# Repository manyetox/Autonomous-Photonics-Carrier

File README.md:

# Autonomous-Photonics-Carrier

**A source-available mobile robotics platform for autonomous and reconfigurable free-space photonics experiments.**

This repository contains the electronics, fabrication files, preliminary embedded firmware, and research documentation for my UCL Electrical and Electronic Engineering third-year BEng project. The carrier is intended to move standard optical hardware around a tabletop, estimate its own motion from complementary sensors, and ultimately support closed-loop optical experiment setup and alignment.

> **Project status — 29 October 2026:** **Platform V2 works**, including the motors, BNO086 IMU, and PAW3395 optical-flow sensor. The **MA730 magnetic encoders remain untested because of component-ordering delays**. **Platform V3 is now in development**, replacing the BNO086 with a lower-cost **STMicroelectronics LSM6DS3**. V3 hardware and firmware validation, full multi-sensor autonomy, and quantitative positioning experiments remain in progress. See the [V3 development notes](docs/platform-v3.md).

<p align="center">
  
  &nbsp;&nbsp;
  
</p>

<p align="center"><em>Platform V2 photographed during assembly. V2 has since been reported working; magnetic-encoder testing is still awaiting components. These photographs show V2, not the developing V3.</em></p>

## Read this first: platform versions are not board revisions

The carrier now has **three platform generations**, with V3 under development:

| System generation | Meaning | Status |
|---|---|---|
| **Platform V1** | First integrated/monolithic autonomous-photonics carrier electronics | Historical, validated, superseded by V2 |
| **Platform V2** | Modular carrier with BNO086 IMU | Working prototype; magnetic encoders still untested |
| **Platform V3** | Next carrier generation with lower-cost LSM6DS3 IMU | In development; see [V3 notes](docs/platform-v3.md) |

The numbers on individual V2 PCBs are **board-local revisions**, not new carrier generations. For example, **OFS-R2.1.1** means *Optical-Flow Sensor board revision 2.1.1*; it is still part of **Platform V2**. The same applies to **MB-R2.1**, **MDI-R2.0**, and **ENC-R1.0**.

See [`VERSIONING.md`](VERSIONING.md) before using fabrication files.

## Why this project exists

Free-space optical experiments are normally assembled and aligned manually. Even a simple setup can require repeated positioning of posts, lenses, polarisers, sources, detectors, and cameras. The long-term research question behind this project is whether a low-cost fleet of mobile optomechanical carriers can make parts of that process **reconfigurable, repeatable, measurable, and eventually autonomous**.

This repository focuses on the carrier layer: motion, embedded electronics, local sensing, and the interfaces needed for higher-level perception and closed-loop experiment control. It does **not** claim that autonomous optical alignment has already been solved; that is the experimental work this platform is intended to enable.

## Research questions

The project is being developed as an experimental research platform rather than only as a mobile-robot hardware build. The central question is:

> **Can a self-propelled optical post-holder module combine mobile positioning, multi-sensor localisation, and optical feedback to autonomously reconstruct and align repeatable free-space photonics experiments?**

The current evaluation is organised around six questions:

1. **Coarse positioning accuracy and repeatability** — How accurately can a carrier reach a commanded planar pose \((x, y, \psi)\), and how closely can it return to that pose over repeated trials? How are the results affected by approach direction, travel distance, wheel slip, payload, and table-surface conditions?
2. **Stationary stability** — How much translational and angular drift occurs while the carrier remains stationary on its wheels? How are the results affected by motor-hold strategy, payload centre of mass, battery voltage, and measurement duration?
3. **Localisation and sensor fusion** — What accuracy and robustness can be achieved using the MA730 wheel encoders, PAW3395 optical-flow sensor, BNO086 (V2) or LSM6DS3 (V3) IMU, and planned overhead visual fiducials individually and in combination? In particular, can the fused estimate remain useful during wheel slip, short visual occlusion, and accumulated odometry drift?
4. **Closed-loop optical alignment and recovery** — Can optical feedback compensate for the residual mechanical error remaining after mobile positioning? What alignment error, convergence time, capture range, success rate, and recovery behaviour can be achieved?
5. **Experiment reconstruction and operating range** — Can one or more carriers reconstruct the same optical configuration on separate occasions and reproduce the same measurement? For which beam sizes, propagation distances, wavelengths, and classes of tabletop experiment is the achieved positioning performance sufficient?
6. **Compatibility, cost, and scalability** — Can the platform carry standard optical posts and common holders without permanent modification? What payload, centre-of-mass height, battery runtime, and cost per carrier are practical, and how does operation change when multiple carriers share the same workspace?

These questions are intended to map directly onto measurable experiments. Results will only be reported after the relevant mechanical, electronic, localisation, and optical-control subsystems have been implemented and experimentally characterised.

> **Design-evolution note:** the earliest research framing included an on-carrier screw-and-flexure fine-positioning stage and UWB ranging. Those ideas belong to the earlier design direction and are **not core Platform V2 subsystems**. Platform V2 instead focuses on a modular mobile carrier using wheel encoding, bottom optical flow, inertial sensing, planned overhead visual localisation, and later optical feedback. Fine optomechanical correction can be evaluated as a separate layer if required.

## Working Platform V2 architecture

```mermaid
flowchart LR
    B["1S LiPo / external power"] --> MB["MB-R2.1<br/>ESP32-WROOM-32UE mainboard"]
    MB --> MDI["MDI-R2.0<br/>TC78H651 + BNO086"]
    MDI --> LM["Left DC gearmotor"]
    MDI --> RM["Right DC gearmotor"]

    MB --> OFS["OFS-R2.1.1<br/>PAW3395 optical-flow board"]
    MB --> ENC["ENC-R1.0<br/>MA730 wheel encoder boards"]

    OFS --> REL["Relative tabletop motion"]
    ENC --> WHEEL["Wheel angle / odometry"]
    MDI --> IMU["Inertial orientation / motion"]

    CAM["Overhead camera + fiducials<br/>planned system layer"] --> HOST["Host perception + experiment software<br/>planned"]
    HOST --> MB

    REL --> FUSION["Pose estimation / sensor fusion<br/>planned"]
    WHEEL --> FUSION
    IMU --> FUSION
    CAM --> FUSION
```

The V2 redesign deliberately separates functions across small PCBs. This makes the system easier to manufacture, debug, replace, and revise than V1's dense integrated board.

### V2 hardware at a glance

| Board ID | Function | Key devices | PCB | Current state |
|---|---|---|---|---|
| **MB-R2.1** | Main controller / power / breakout | ESP32-WROOM-32UE, NCP186 3.3 V LDO | 4-layer, ~25 × 27.1 mm | **Validated** |
| **MDI-R2.0** | Dual motor drive + IMU | TC78H651FGN, BNO086 | 4-layer, ~25 × 27 mm | **Validated** |
| **OFS-R2.1.1** | Bottom optical-flow sensing | PAW3395, AP2127K-1.8 | 2-layer, ~19.3 × 24.0 mm | **Working, author-confirmed** |
| **ENC-R1.0** | Wheel-angle sensing | MA730 magnetic encoder | 2-layer, ~20 × 16.8 mm | **Untested; component ordering delayed** |

<p align="center"><em>Platform V2 design render. V2 uses a modular electronics architecture so sensing, motor control, and the main controller can be manufactured, debugged, and revised independently.</em></p>

## Design evolution

### Platform V3 — lower-cost IMU, in development

V3 replaces the V2 BNO086 with the **STMicroelectronics LSM6DS3**, identified in the latest schematic discussion. This is a six-axis accelerometer/gyroscope; V3 needs a matching driver and host-side orientation estimation instead of the BNO086 rotation-vector interface. The supplied [V3 hardware](hardware/platform-v3/README.md) includes the two-layer MDI-R3.0 motor/IMU board and OFS-R2.2 optical board. See [V3 development notes](docs/platform-v3.md).

### Platform V1 — integrated architecture

V1 placed most functions on one approximately **50 × 50 mm, 8-layer PCB**. The design included an **ESP32-S3-WROOM-1**, **DWM3000 UWB**, **BNO086 IMU**, **two TMC5041 stepper-controller ICs**, **DRV8231 motor-driver stages**, and the associated power and USB circuitry. It was a useful integration exercise and was built around the original concept of combining coarse mobile motion with local stepper/flexure positioning.

<p align="center"><em>Platform V1 concept. The first carrier generation combined the mobile base with local optomechanical positioning and concentrated most of the electronics onto a single integrated PCB.</em></p>

### Why V2 changed direction

The current architecture intentionally moves away from putting every possible function on one carrier PCB. The main reasons were:

- **Modularity:** sensor and motor electronics can be revised without remanufacturing the controller.
- **Debuggability:** faults can be isolated board-by-board.
- **Lower manufacturing risk:** smaller boards and fewer tightly coupled subsystems.
- **Sensor strategy:** PAW3395 relative optical tracking, MA730 wheel angle, BNO086 inertial data, and planned overhead fiducials provide complementary information without retaining UWB as a core requirement.
- **Fine alignment separation:** the mobile base focuses on coarse positioning and repeatability. Very fine optical correction can be implemented as a separate optomechanical layer instead of forcing stepper/flexure hardware into every mobile carrier.
- **Cost and repeatability:** the architecture is intended to scale to multiple carriers, so unnecessary per-carrier complexity matters.

The V1 source is retained because it documents the design path and may still be useful to researchers interested in a more integrated architecture.

### Legacy reference — pre-project mobile robotics hardware

Before the dedicated photonics-carrier generations, I developed a more general mobile-robot electronics platform. It is retained in [`hardware/legacy-reference`](hardware/legacy-reference/) because several practical design lessons carried into this project, but it is **not Platform V0** and should not be treated as part of the carrier version sequence.

<p align="center"><em>Legacy mobile-robot reference design retained for engineering context. It predates the autonomous-photonics carrier and is included only to document relevant design heritage.</em></p>

## Repository map

```text
Autonomous-Photonics-Carrier/
├── hardware/
│   ├── platform-v1/                 # Historical integrated carrier
│   ├── platform-v2/
│   │   ├── mainboard/MB-R2.1/
│   │   ├── motor-driver-imu/MDI-R2.0/
│   │   ├── optical-flow/OFS-R2.1.1/
│   │   └── wheel-encoder/ENC-R1.0/
│   ├── platform-v3/                 # MDI-R3.0 and OFS-R2.2 development files
│   └── legacy-reference/            # Pre-project robot electronics; not a platform version
├── firmware/
│   ├── platform-v2/agent-v2.4/       # Latest local V2 firmware and client
│   ├── platform-v3/                  # LSM6DS3 firmware pending
│   └── preliminary/                  # Original scaffold retained
├── software/                        # Planned host-side autonomy / experiment software
├── docs/                            # Architecture, methods, validation, manufacturing notes
├── data/                            # Experimental-data conventions; no results claimed yet
├── media/                           # Image/video placeholders
├── VERSIONING.md
├── CHANGELOG.md
├── CITATION.cff
└── LICENSE.md
```

## Hardware source and fabrication files

Native **KiCad source files** are provided alongside fabrication outputs. Current fabrication packages are separated from superseded board revisions so that a Gerber revision cannot be mistaken for a platform generation.

Start here:

- [Platform V1 hardware](hardware/platform-v1/README.md)
- [Platform V2 hardware](hardware/platform-v2/README.md)
- [Platform V3 development hardware](hardware/platform-v3/README.md)
- [V2 mainboard — MB-R2.1](hardware/platform-v2/mainboard/MB-R2.1/README.md)
- [Motor/IMU — MDI-R2.0](hardware/platform-v2/motor-driver-imu/MDI-R2.0/README.md)
- [Optical flow — OFS-R2.1.1](hardware/platform-v2/optical-flow/OFS-R2.1.1/README.md)
- [Wheel encoder — ENC-R1.0](hardware/platform-v2/wheel-encoder/ENC-R1.0/README.md)
- [Manufacturing guide](docs/manufacturing.md)

The CSV BOMs in the board folders were auto-extracted from the KiCad PCB files to make review easier. **They are not a substitute for checking the schematic and part datasheets before ordering.**

## Published V2 firmware

The latest local [Agent v2.4 package](firmware/platform-v2/agent-v2.4/README.md) is included for **ESP32 + BNO086 + PAW3395**. It includes web controls, independent motor factors, level/origin calibration, relative positioning, telemetry and an Open WebUI client. ESP32 compilation and host checks are documented with the package; the author’s working-V2 report does not validate every automated action. [V3 LSM6DS3 firmware remains pending](firmware/platform-v3/README.md).

## Original preliminary firmware

A deliberately conservative PlatformIO/Arduino scaffold is included in [`firmware/preliminary`](firmware/preliminary/README.md). It establishes the intended embedded-software structure, status reporting, motor-control abstraction, serial command interface, and placeholders for BNO086, PAW3395, and MA730 integration.

It is **not the final autonomy firmware** and it is **not presented as experimentally validated software**. Peripheral signal-to-GPIO assignment is left disabled by default wherever the uploaded hardware files do not prove the final system interconnect unambiguously. This prevents a public repository from presenting guessed pin mappings as fact.

The preliminary firmware and parts of the repository/software scaffolding were prepared with assistance from **OpenAI ChatGPT 5.6** and then reviewed against the project hardware files. See [`AI_ASSISTANCE.md`](AI_ASSISTANCE.md).

## Planned sensing and autonomy stack

The intended estimation hierarchy is complementary rather than relying on a single sensor:

1. **Wheel angle / odometry:** MA730 magnetic encoders provide direct rotational information at the drivetrain.
2. **Bottom optical flow:** PAW3395 provides high-rate relative motion against the tabletop and can expose wheel-slip/odometry disagreement.
3. **IMU:** BNO086 provides the V2 inertial input; V3 adopts LSM6DS3 acceleration and angular-rate data with orientation estimation in firmware.
4. **Overhead fiducials:** a camera observing AprilTags or similar fiducials is planned as a global absolute pose reference and recovery mechanism.
5. **Optical feedback:** experimental signals can eventually be incorporated into the control loop so the carrier optimises the *optical result*, not only geometric pose.

Prototype IMU/optical-flow positioning firmware has been developed in the project. Global localisation, encoder integration, multi-carrier coordination, and optical-feedback optimisation remain development work; measured positioning performance has not yet been published.

## Research measurements this platform is intended to support

The repository is organised so that later results can be reproduced rather than reported only as a final demo. The principal measurements are:

- planar pose accuracy in **x, y, and yaw** against an external reference;
- **return-to-pose repeatability** over repeated move-away-and-return cycles;
- **stationary drift** and accumulated odometry drift;
- wheel-encoder, optical-flow, and IMU disagreement under controlled motion;
- recovery from deliberate slip or localisation error;
- carrier-to-carrier consistency if multiple units are built;
- cost per carrier and sensitivity to inexpensive mechanical components;
- success rate of a defined optical alignment task.

See [`docs/research-methodology.md`](docs/research-methodology.md) and [`docs/validation.md`](docs/validation.md). Until those experiments are complete, target resolutions or simulated estimates should not be read as measured performance.

For the research context behind the architecture, see [`docs/related-work.md`](docs/related-work.md).

## Research context and selected related work

This project sits between **robotic optical alignment**, **autonomous laboratories**, and **mobile multi-sensor robotics**. The most directly relevant prior work is summarised here; the longer discussion belongs in [`docs/related-work.md`](docs/related-work.md).

- **OptoMate / AI-Driven Robotics for Optics** demonstrates a general-purpose robotic approach to physically assembling and aligning free-space optical experiments using computer vision, robotic manipulation, and AI-assisted control [1]. It is a particularly close research neighbour, but it uses an external robotic manipulator rather than making each optical element independently mobile.
- **Choi et al.** present a closed-loop framework for robotic optical assembly, alignment, and self-recovery [2]. This is directly relevant to the carrier's long-term objective of detecting misalignment, correcting it from measurement feedback, and recovering after a disturbance.
- **Rakhmatulin et al.** review automated laser-optics alignment, including optimisation and machine-learning approaches [3]. Their review motivates treating the optical signal itself as a feedback variable rather than assuming that geometric positioning alone is sufficient.
- **Fang and Savransky** show automated alignment of a reconfigurable optical system using focal-plane sensing and Kalman filtering [4], providing an example of image-based estimation driving corrective optical motion.
- **Szymanski et al.** demonstrate the broader self-driving-laboratory concept in which robotics, measurement, and computational decision-making form a closed experimental loop [5]. The present project explores a different physical layer: making the experimental optical hardware itself reconfigurable on the tabletop.

Commercial active-alignment systems from companies such as Physik Instrumente provide useful industrial context: high-precision automated optical alignment is already practical, but such systems are generally built around dedicated stages and predefined alignment tasks rather than low-cost independently mobile optical carriers [6].

The distinction matters: this repository does **not** claim that the individual techniques above are new. The research question is whether coarse mobile positioning, complementary low-cost sensing, standard optomechanical compatibility, and closed-loop optical feedback can be combined into a scalable carrier architecture for reconfigurable free-space experiments.

## Selected references

1. S. Z. Uddin, S. Vaidya, S. Choudhary, Z. Chen, R. K. Salib, L. Huang, D. R. Englund, and M. Soljačić, **“AI-Driven Robotics for Optics,”** arXiv:2505.17985, 2025. https://doi.org/10.48550/arXiv.2505.17985
2. S. Choi, S. Vaidya, C. Silva, S. Z. Uddin, S. B. Shuvo, S. Choudhary, and M. Soljačić, **“A Framework for Closed-Loop Robotic Assembly, Alignment and Self-Recovery of Precision Optical Systems,”** arXiv:2603.21496, 2026. https://doi.org/10.48550/arXiv.2603.21496
3. I. Rakhmatulin, D. Risbridger, R. Carter, M. J. D. Esser, and M. S. Erden, **“A Review of Automation of Laser Optics Alignment with a Focus on Machine Learning Applications,”** *Optics and Lasers in Engineering*, vol. 173, 107923, 2024. https://doi.org/10.1016/j.optlaseng.2023.107923
4. J. Fang and D. Savransky, **“Automated Alignment of a Reconfigurable Optical System Using Focal-Plane Sensing and Kalman Filtering,”** arXiv:1608.07550, 2016. https://arxiv.org/abs/1608.07550
5. N. J. Szymanski *et al.*, **“An Autonomous Laboratory for the Accelerated Synthesis of Inorganic Materials,”** *Nature*, vol. 624, pp. 86–91, 2023. https://doi.org/10.1038/s41586-023-06734-w
6. PI (Physik Instrumente), **“Active Photonics Alignment Systems / Fiber Optic Alignment Stages,”** product and application documentation. https://www.pi-usa.us/en/products/photonics-alignment-solutions

## Project information

**Author:** Taylan Arslan  
**Programme:** UCL Electrical and Electronic Engineering — BEng third-year project, 2026–27  
**Project supervisor:** Prof. Kaan Akşit  
**EEE co-supervisor:** Thomas Gilbert

The supervisors are acknowledged for academic supervision; this repository is maintained by the author and is **not an official UCL product or endorsement**.

## Contributing

Research feedback, reproducibility reports, bug findings, and non-commercial improvements are welcome. Please read [`CONTRIBUTING.md`](CONTRIBUTING.md) before opening a pull request. In particular, use the versioning vocabulary above when discussing hardware revisions.

## Licensing

This repository is intentionally **source-available for non-commercial research, education, and personal experimentation**, but it does **not** grant commercial-use rights under its public licences.

- Hardware design files, documentation, diagrams, and repository media: **CC BY-NC 4.0**.
- Firmware and software: **PolyForm Noncommercial License 1.0.0**.
- Commercial use requires a **separate written commercial licence** from the author.

Because of the non-commercial restriction, this project should **not** be described as OSHWA-compliant “open-source hardware.” See [`LICENSE.md`](LICENSE.md) for the exact scope and important IP limitations.

## Safety and experimental responsibility

This is research hardware, not a certified product. Re-check power rails, polarity, motor current, battery protection/charging, connector orientation, clearances, and fabrication outputs before use. If the carrier is used around lasers or other optical sources, follow the laboratory's laser-safety procedures; this repository does not replace a risk assessment or device datasheet.

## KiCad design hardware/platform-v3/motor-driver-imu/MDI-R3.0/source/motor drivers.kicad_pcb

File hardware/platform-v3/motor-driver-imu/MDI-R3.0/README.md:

# MDI-R3.0 — motor driver + LSM6DS3

**Platform:** V3 development snapshot  
**Status:** unvalidated development design  
**PCB:** two copper layers

Replaces the V2 BNO086 with LSM6DS3 and reduces the motor/IMU PCB from four copper layers to two. The PCB is marked V3.0. The schematic contains the TC78H651FNG motor-driver symbol; its component value is `~`, so the exact purchasing code still needs BOM review.

## Files

- `source/`: supplied native KiCad project, schematic and PCB; original filenames retained.
- [Component CSV](bom/components-from-schematic.csv): extracted from the schematic, not a verified purchasing BOM.
- `fabrication/supplied/`: supplied Gerber/drill outputs.

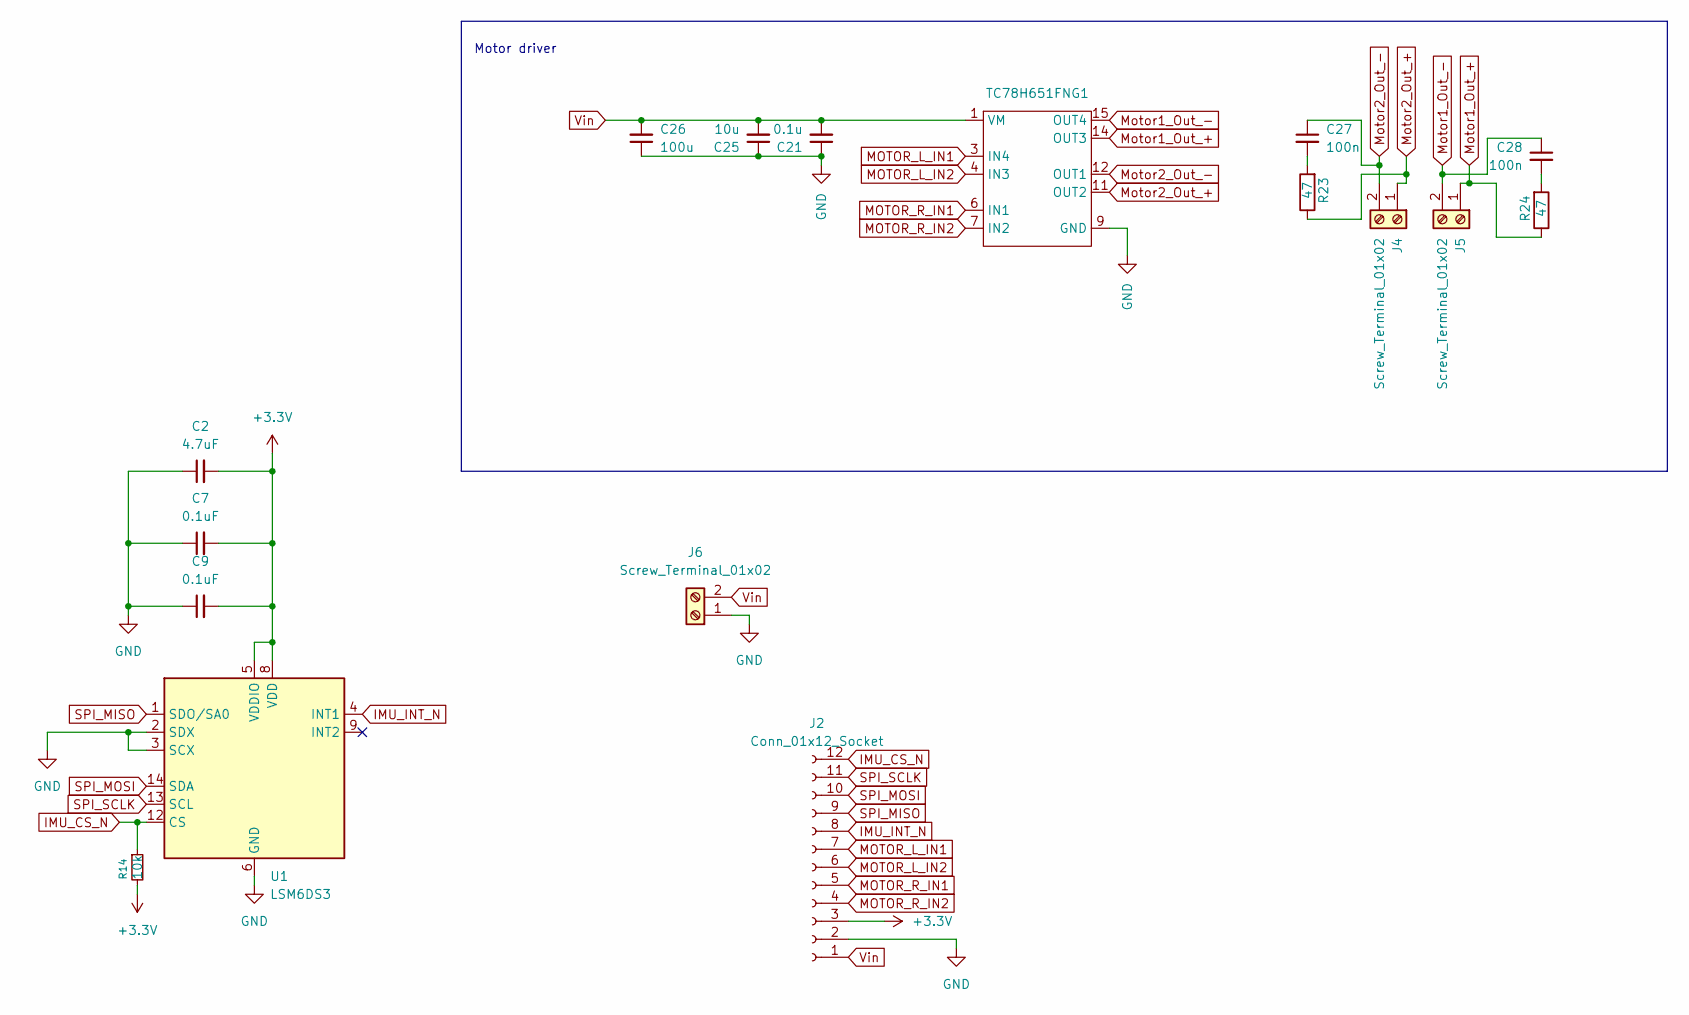
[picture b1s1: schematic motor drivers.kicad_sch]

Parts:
C2: 4.7uF; C_0805_2012Metric_Pad1.18x1.45mm_HandSolder
C7, C9: 0.1uF; C_0603_1608Metric
C21: 0.1u; C_0805_2012Metric_Pad1.18x1.45mm_HandSolder; LCSC Part # C14663
C25: 10u; C_0805_2012Metric_Pad1.18x1.45mm_HandSolder; LCSC Part # C5464883
C26: 100u; C_1206_3216Metric_Pad1.33x1.80mm_HandSolder; LCSC Part # C5464883
C27, C28: 100n; C_0603_1608Metric; LCSC Part # C14663
J2: Conn_01x12_Socket; PinHeader_1x12_P1.00mm_Vertical
J4, J5, J6: Screw_Terminal_01x02; power pad dual
R14: 10k; R_0603_1608Metric_Pad0.98x0.95mm_HandSolder
R23, R24: 47; R_0603_1608Metric; LCSC Part # C23182
TC78H651FNG1: TSSOP-16_4.4x5mm_P0.65mm
U1: LSM6DS3; LGA-14_3x2.5mm_P0.5mm_LayoutBorder3x4y

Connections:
+3.3V: C2.2, C7.2, C9.2, J2.3, R14.2, U1.5 (VDDIO), U1.8 (VDD)
GND: C2.1, C7.1, C9.1, C21.1, C25.1, C26.1, J2.2, J6.1, TC78H651FNG1.9 (GND), U1.2 (SDX), U1.3 (SCX), U1.6 (GND), U1.7 (GND)
IMU_CS_N: J2.12, R14.1, U1.12 (CS)
IMU_INT_N: J2.8, U1.4 (INT1)
MOTOR_L_IN1: J2.7, TC78H651FNG1.3 (IN4)
MOTOR_L_IN2: J2.6, TC78H651FNG1.4 (IN3)
MOTOR_R_IN1: J2.5, TC78H651FNG1.6 (IN1)
MOTOR_R_IN2: J2.4, TC78H651FNG1.7 (IN2)
Motor1_Out_+: J5.1, R24.1, TC78H651FNG1.14 (OUT3)
Motor1_Out_-: C28.1, J5.2, TC78H651FNG1.15 (OUT4)
Motor2_Out_+: J4.1, R23.1, TC78H651FNG1.11 (OUT2)
Motor2_Out_-: C27.1, J4.2, TC78H651FNG1.12 (OUT1)
unnamed: C27.2, R23.2
unnamed: C28.2, R24.2
SPI_MISO: J2.9, U1.1 (SDO/SA0)
SPI_MOSI: J2.10, U1.14 (SDA)
SPI_SCLK: J2.11, U1.13 (SCL)
Vin: C21.2, C25.2, C26.2, J2.1, J6.2, TC78H651FNG1.1 (VM)

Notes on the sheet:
Motor driver

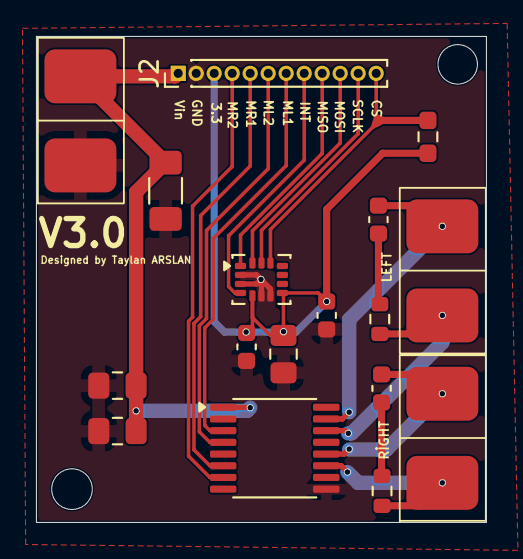
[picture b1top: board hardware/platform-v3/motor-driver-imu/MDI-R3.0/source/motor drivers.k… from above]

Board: 2 copper layers, 25.0 x 27.0 mm, 17 parts (0 on the bottom side), 18 nets.

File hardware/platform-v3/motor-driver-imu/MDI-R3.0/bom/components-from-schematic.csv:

Reference,Value,Footprint,Datasheet
C2,4.7uF,Capacitor_SMD:C_0805_2012Metric_Pad1.18x1.45mm_HandSolder,
C7,0.1uF,Capacitor_SMD:C_0603_1608Metric,
C9,0.1uF,Capacitor_SMD:C_0603_1608Metric,
C21,0.1u,Capacitor_SMD:C_0805_2012Metric_Pad1.18x1.45mm_HandSolder,
C25,10u,Capacitor_SMD:C_0805_2012Metric_Pad1.18x1.45mm_HandSolder,
C26,100u,Capacitor_SMD:C_1206_3216Metric_Pad1.33x1.80mm_HandSolder,
C27,100n,Capacitor_SMD:C_0603_1608Metric,
C28,100n,Capacitor_SMD:C_0603_1608Metric,
J2,Conn_01x12_Socket,Connector_PinHeader_1.00mm:PinHeader_1x12_P1.00mm_Vertical,
J4,Screw_Terminal_01x02,Library-kicad:power pad dual,
J5,Screw_Terminal_01x02,Library-kicad:power pad dual,
J6,Screw_Terminal_01x02,Library-kicad:power pad dual,
R14,10k,Resistor_SMD:R_0603_1608Metric_Pad0.98x0.95mm_HandSolder,
R23,47,Resistor_SMD:R_0603_1608Metric,
R24,47,Resistor_SMD:R_0603_1608Metric,
TC78H651FNG1,~,Package_SO:TSSOP-16_4.4x5mm_P0.65mm,
U1,LSM6DS3,Package_LGA:LGA-14_3x2.5mm_P0.5mm_LayoutBorder3x4y,https://www.st.com/resource/en/datasheet/lsm6ds3tr-c.pdf

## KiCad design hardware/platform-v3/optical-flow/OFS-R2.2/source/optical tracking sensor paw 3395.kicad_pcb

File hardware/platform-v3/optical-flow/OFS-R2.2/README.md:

# OFS-R2.2 — PAW3395 optical flow

**Platform:** V3 development snapshot  
**Status:** unvalidated development design  
**PCB:** two copper layers

The PCB is marked V2.2 and uses two copper layers. This is the revised optical-flow board supplied with the V3 development files; the author-confirmed working V2 sensor does not establish validation of this revision.

## Files

- `source/`: supplied native KiCad project, schematic and PCB; original filenames retained.
- [Component CSV](bom/components-from-schematic.csv): extracted from the schematic, not a verified purchasing BOM.
- `fabrication/supplied/`: supplied Gerber/drill outputs.

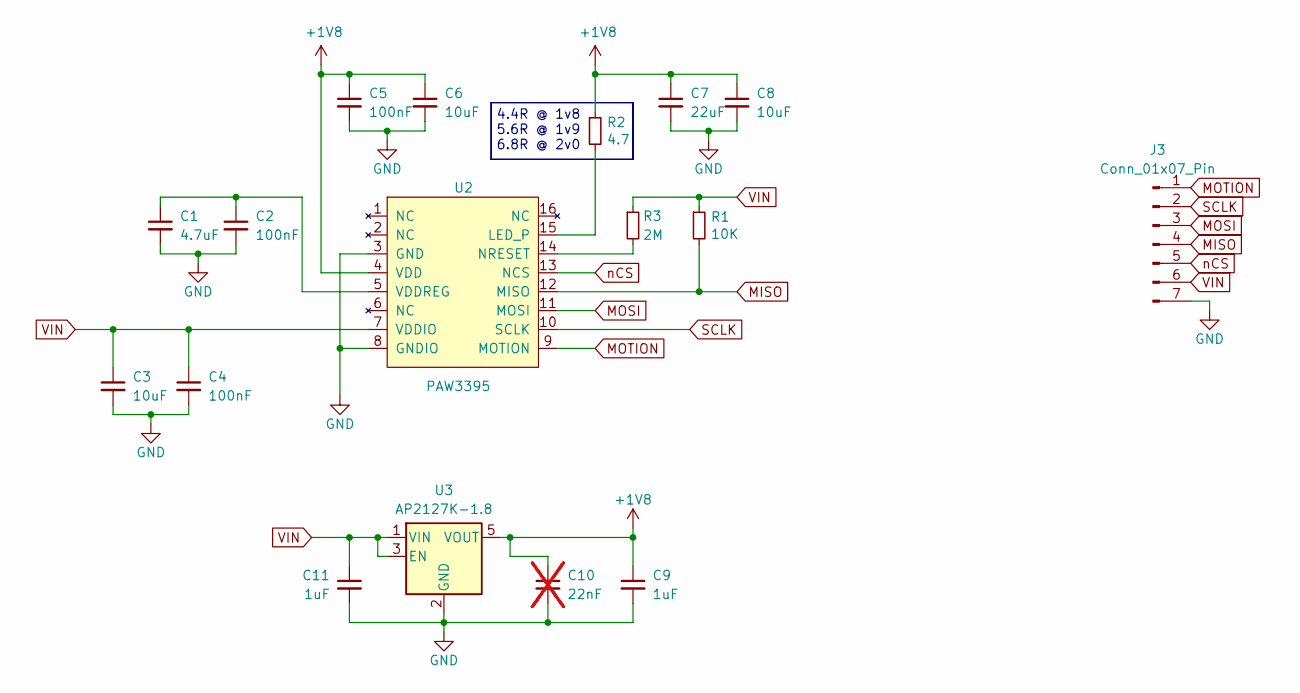
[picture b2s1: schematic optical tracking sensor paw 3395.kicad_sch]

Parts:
C1: 4.7uF; C_0805_2012Metric
C2, C4, C5: 100nF; C_0603_1608Metric
C3, C8: 10uF; C_0805_2012Metric
C6: 10uF; C_0603_1608Metric
C7: 22uF; C_1206_3216Metric
C9, C11: 1uF; C_0603_1608Metric
C10: 22nF; C_0603_1608Metric; not fitted
J3: Conn_01x07_Pin; PinHeader_1x07_P1.00mm_Vertical
R1: 10K; R_0603_1608Metric; LCSC C25804
R2: 4.7; R_0603_1608Metric; LCSC C23164
R3: 2M; R_0603_1608Metric; LCSC C22976
U2: PAW3395
U3: AP2127K-1.8; SOT-23-5

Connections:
+1V8: C5.1, C6.1, C7.1, C8.1, C9.1, C10.1, R2.1, U2.4 (VDD), U3.5 (VOUT)
GND: C1.2, C2.2, C3.2, C4.2, C5.2, C6.2, C7.2, C8.2, C9.2, C10.2, C11.2, J3.7, U2.3 (GND), U2.8 (GNDIO), U3.2 (GND)
MISO: J3.4, R1.2, U2.12 (MISO)
MOSI: J3.3, U2.11 (MOSI)
MOTION: J3.1, U2.9 (MOTION)
unnamed: R2.2, U2.15 (LED_P)
unnamed: R3.2, U2.14 (NRESET)
unnamed: C1.1, C2.1, U2.5 (VDDREG)
SCLK: J3.2, U2.10 (SCLK)
VIN: C3.1, C4.1, C11.1, J3.6, R1.1, R3.1, U2.7 (VDDIO), U3.1 (VIN), U3.3 (EN)
nCS: J3.5, U2.13 (NCS)

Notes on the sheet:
4.4R @ 1v8 5.6R @ 1v9 6.8R @ 2v0

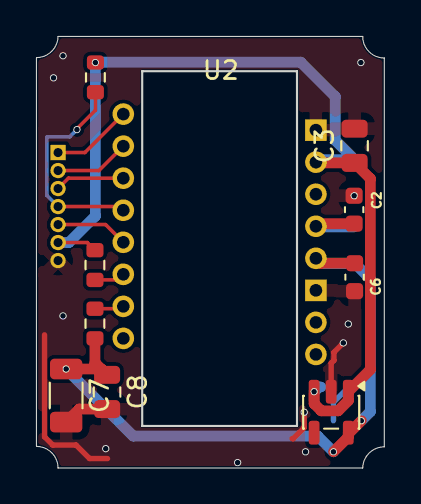
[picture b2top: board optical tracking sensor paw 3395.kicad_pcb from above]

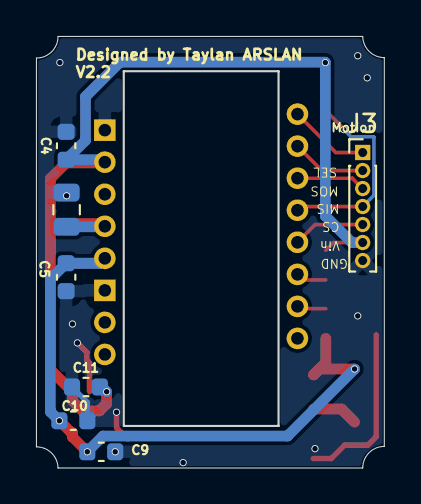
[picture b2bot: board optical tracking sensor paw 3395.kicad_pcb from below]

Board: 2 copper layers, 19.3 x 24.0 mm, 17 parts (7 on the bottom side), 11 nets.

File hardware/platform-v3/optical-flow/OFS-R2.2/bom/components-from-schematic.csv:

Reference,Value,Footprint,Datasheet
C1,4.7uF,Capacitor_SMD:C_0805_2012Metric,
C2,100nF,Capacitor_SMD:C_0603_1608Metric,
C3,10uF,Capacitor_SMD:C_0805_2012Metric,
C4,100nF,Capacitor_SMD:C_0603_1608Metric,
C5,100nF,Capacitor_SMD:C_0603_1608Metric,
C6,10uF,Capacitor_SMD:C_0603_1608Metric,
C7,22uF,Capacitor_SMD:C_1206_3216Metric,
C8,10uF,Capacitor_SMD:C_0805_2012Metric,
C9,1uF,Capacitor_SMD:C_0603_1608Metric,
C10,22nF,Capacitor_SMD:C_0603_1608Metric,
C11,1uF,Capacitor_SMD:C_0603_1608Metric,
J3,Conn_01x07_Pin,Connector_PinHeader_1.00mm:PinHeader_1x07_P1.00mm_Vertical,
R1,10K,Resistor_SMD:R_0603_1608Metric,
R2,4.7,Resistor_SMD:R_0603_1608Metric,
R3,2M,Resistor_SMD:R_0603_1608Metric,
U2,PAW3395,Library-kicad:PAW3395,
U3,AP2127K-1.8,Package_TO_SOT_SMD:SOT-23-5,https://www.diodes.com/assets/Datasheets/AP2127.pdf

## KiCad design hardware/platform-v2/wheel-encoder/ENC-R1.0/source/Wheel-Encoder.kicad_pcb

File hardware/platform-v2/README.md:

# Platform V2 — working modular prototype

Platform V2 is the working modular carrier baseline; Platform V3 is now in development. It is a **system generation**, not a PCB revision number.

Current boards:

- **MB-R2.1** — main controller/power/breakout
- **MDI-R2.0** — motor driver + BNO086 IMU
- **OFS-R2.1.1** — PAW3395 optical-flow sensor
- **ENC-R1.0** — MA730 wheel encoder

As of 29 October 2026, the author confirms V2 works, including the motors, BNO086 IMU, and PAW3395 optical-flow sensor. The MA730 magnetic encoders remain **untested because of component-ordering delays**.

Earlier documentation incorrectly labelled the encoder as validated and optical flow as unvalidated. These status records are corrected; measured positioning accuracy is still to be established.

These files describe V2 hardware. The lower-cost LSM6DS3 belongs to [V3 development](../../docs/platform-v3.md), not to the unchanged MDI-R2.0 board.

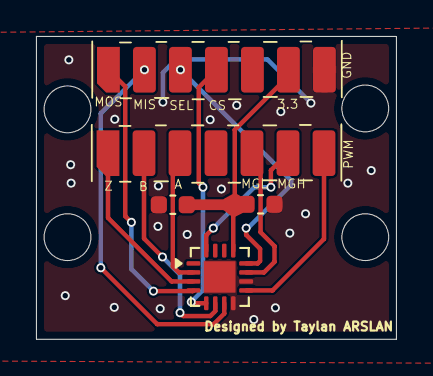
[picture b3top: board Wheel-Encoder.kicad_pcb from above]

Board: 2 copper layers, 20.0 x 16.8 mm, 5 parts (0 on the bottom side), 12 nets.

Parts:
C1: 1u; C_0603_1608Metric
C2: 100n; C_0603_1608Metric
J1, J2: Conn_01x07_Socket; 7 pin smd conn 2.54
U1: MA730; QFN-16-1EP_3x3mm_P0.5mm_EP1.75x1.75mm

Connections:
+3.3V: C1.2, C2.2, J1.6, U1.13 (VDD)
A: J2.3, U1.2 (A)
B: J2.2, U1.6 (B)
CS: J1.4, U1.5 (~CS)
GND: C1.1, C2.1, J1.7, U1.8 (GND), U1.10 (TEST), U1.17 (PAD)
MGH: J2.6, U1.16 (MGH)
MGL: J2.5, U1.11 (MGL)
MISO: J1.2, U1.7 (MISO)
MOSI: J1.1, U1.4 (MOSI)
PWM: J2.7, U1.9 (PWM)
SCLK: J1.3, U1.12 (SCLK)
Z: J2.1, U1.3 (Z)

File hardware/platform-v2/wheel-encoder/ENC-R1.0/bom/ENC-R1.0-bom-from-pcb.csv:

Quantity,References,Value / Part,Footprint,Source
1,C2,100n,Capacitor_SMD:C_0603_1608Metric,Auto-extracted from KiCad PCB; verify against schematic before ordering
1,C1,1u,Capacitor_SMD:C_0603_1608Metric,Auto-extracted from KiCad PCB; verify against schematic before ordering
2,"J1, J2",Conn_01x07_Socket,Library-kicad:7 pin smd conn 2.54,Auto-extracted from KiCad PCB; verify against schematic before ordering
1,U1,MA730,Package_DFN_QFN:QFN-16-1EP_3x3mm_P0.5mm_EP1.75x1.75mm,Auto-extracted from KiCad PCB; verify against schematic before ordering

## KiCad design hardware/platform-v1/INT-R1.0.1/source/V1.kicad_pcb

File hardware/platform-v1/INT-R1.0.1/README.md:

# INT-R1.0.1 — Platform V1 integrated PCB

**Platform:** V1  
**Board revision:** INT-R1.0.1  
**Status:** validated historical hardware; superseded by Platform V2  
**PCB:** 8 layers, approximately 50 × 50 mm

## Main subsystems

- ESP32-S3-WROOM-1 controller
- DWM3000 UWB module
- BNO086 IMU
- 2 × TMC5041 stepper-controller ICs
- 2 × DRV8231 motor-driver stages
- TPS56528DDA power stage
- USB/ESD and breakout interfaces

`source/` contains the editable KiCad files. `fabrication/current/` contains the final retained V1 Gerber/drill package. Earlier schematic export is kept only in `archive/`.

> **Image placeholder:** I will add a V1 board photograph or render here later.

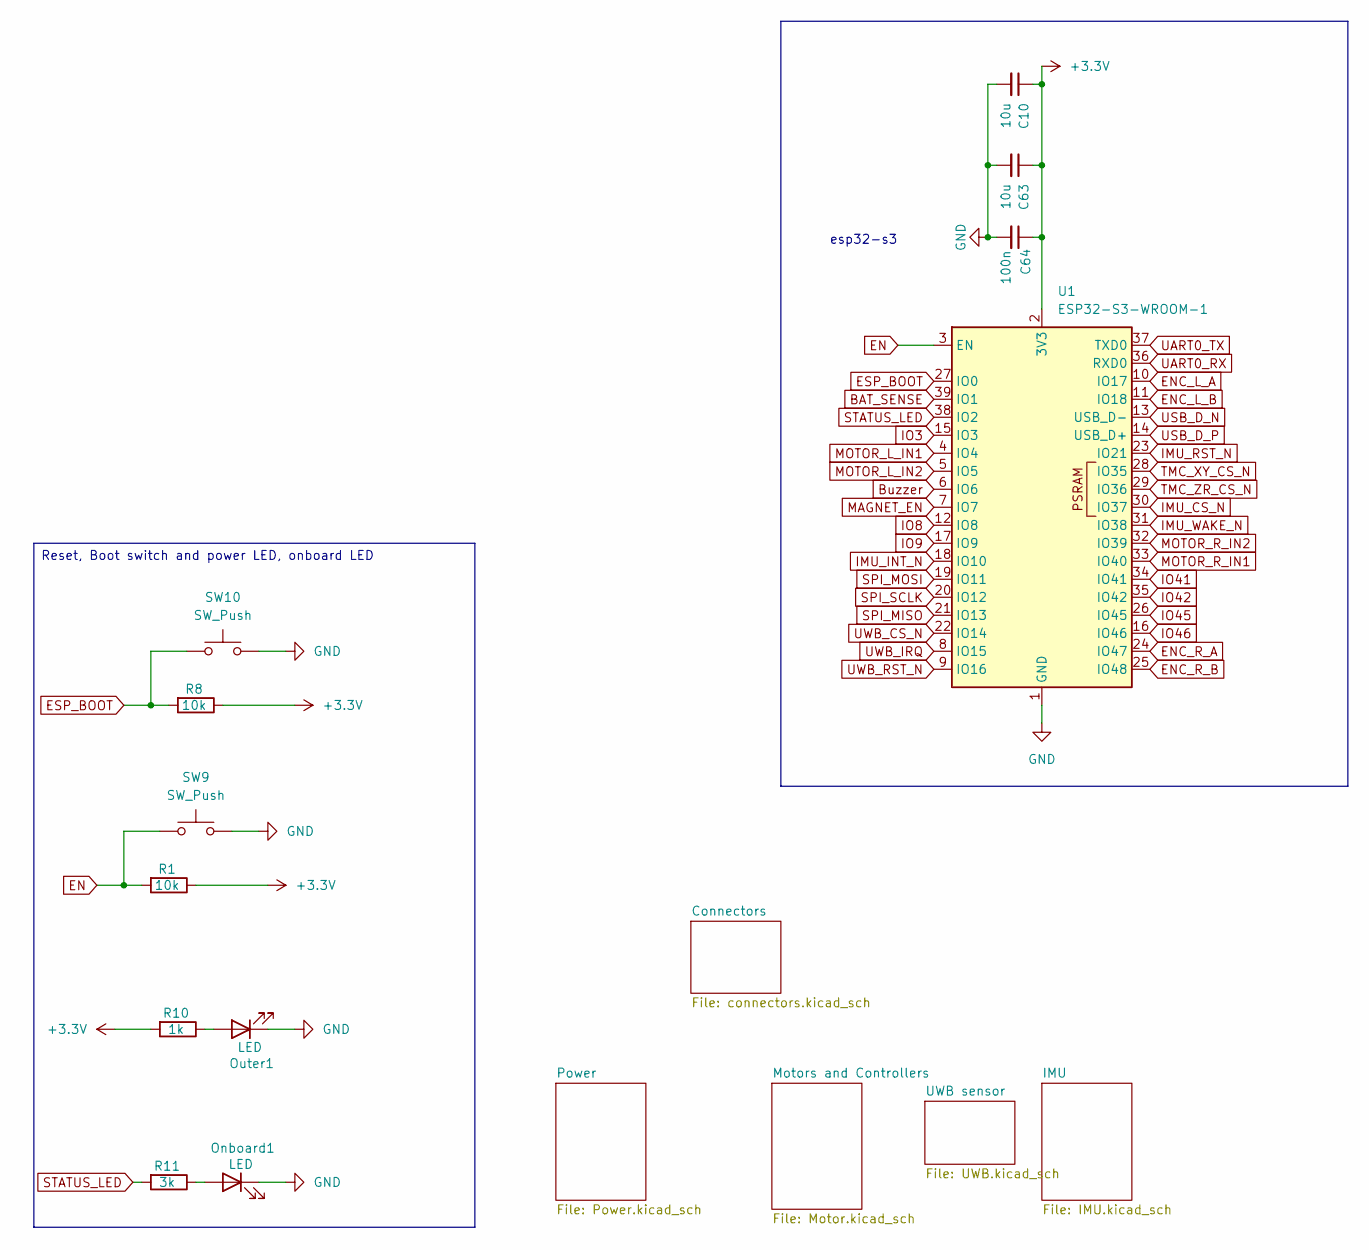
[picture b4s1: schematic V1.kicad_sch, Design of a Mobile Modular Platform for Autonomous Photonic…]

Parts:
C10, C63: 10u; C_0603_1608Metric_Pad1.08x0.95mm_HandSolder; LCSC Part # C15850
C64: 100n; C_0402_1005Metric_Pad0.74x0.62mm_HandSolder; LCSC Part # C15850
Onboard1: LED; LED_0603_1608Metric_Pad1.05x0.95mm_HandSolder; LCSC Part # C2297
Outer1: LED; LED_0603_1608Metric_Pad1.05x0.95mm_HandSolder
R1, R8: 10k; R_0402_1005Metric_Pad0.72x0.64mm_HandSolder; LCSC Part # C21190
R10: 1k; R_0402_1005Metric_Pad0.72x0.64mm_HandSolder; LCSC Part # C21190
R11: 3k; R_0402_1005Metric_Pad0.72x0.64mm_HandSolder; LCSC Part # C4211
SW9, SW10: SW_Push; SW_SPST_CK_KXT3
U1: ESP32-S3-WROOM-1

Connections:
BAT_SENSE: U1.39 (IO1); also elsewhere on the board
Buzzer: U1.6 (IO6); also elsewhere on the board
EN: R1.2, SW9.1, U1.3 (EN); also elsewhere on the board
ENC_L_A: U1.10 (IO17); also elsewhere on the board
ENC_L_B: U1.11 (IO18); also elsewhere on the board
ENC_R_A: U1.24 (IO47); also elsewhere on the board
ENC_R_B: U1.25 (IO48); also elsewhere on the board
ESP_BOOT: R8.2, SW10.1, U1.27 (IO0); also elsewhere on the board
GND: C10.2, C63.2, C64.2, Onboard1.1 (K), Outer1.1 (K), SW9.2, SW10.2, U1.1 (GND), U1.40 (GND), U1.41 (GND); also elsewhere on the board
IMU_CS_N: U1.30 (IO37); also elsewhere on the board
IMU_INT_N: U1.18 (IO10); also elsewhere on the board
IMU_RST_N: U1.23 (IO21); also elsewhere on the board
IMU_WAKE_N: U1.31 (IO38); also elsewhere on the board
IO3: U1.15 (IO3); also elsewhere on the board
IO8: U1.12 (IO8); also elsewhere on the board
IO9: U1.17 (IO9); also elsewhere on the board
IO41: U1.34 (IO41); also elsewhere on the board
IO42: U1.35 (IO42); also elsewhere on the board
IO45: U1.26 (IO45); also elsewhere on the board
IO46: U1.16 (IO46); also elsewhere on the board
MAGNET_EN: U1.7 (IO7); also elsewhere on the board
MOTOR_L_IN1: U1.4 (IO4); also elsewhere on the board
MOTOR_L_IN2: U1.5 (IO5); also elsewhere on the board
MOTOR_R_IN1: U1.33 (IO40); also elsewhere on the board
MOTOR_R_IN2: U1.32 (IO39); also elsewhere on the board
unnamed: Onboard1.2 (A), R11.1
unnamed: Outer1.2 (A), R10.1
PS1: C10.1, C63.1, C64.1, R1.1, R8.1, R10.2, U1.2 (3V3); also elsewhere on the board
SPI_MISO: U1.21 (IO13); also elsewhere on the board
SPI_MOSI: U1.19 (IO11); also elsewhere on the board
SPI_SCLK: U1.20 (IO12); also elsewhere on the board
STATUS_LED: R11.2, U1.38 (IO2)
TMC_XY_CS_N: U1.28 (IO35); also elsewhere on the board
TMC_ZR_CS_N: U1.29 (IO36); also elsewhere on the board
UART0_RX: U1.36 (RXD0); also elsewhere on the board
UART0_TX: U1.37 (TXD0); also elsewhere on the board
USB_D_N: U1.13 (USB_D-); also elsewhere on the board
USB_D_P: U1.14 (USB_D+); also elsewhere on the board
UWB_CS_N: U1.22 (IO14); also elsewhere on the board
UWB_IRQ: U1.8 (IO15); also elsewhere on the board
UWB_RST_N: U1.9 (IO16); also elsewhere on the board

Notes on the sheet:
esp32-s3
Reset, Boot switch and power LED, onboard LED

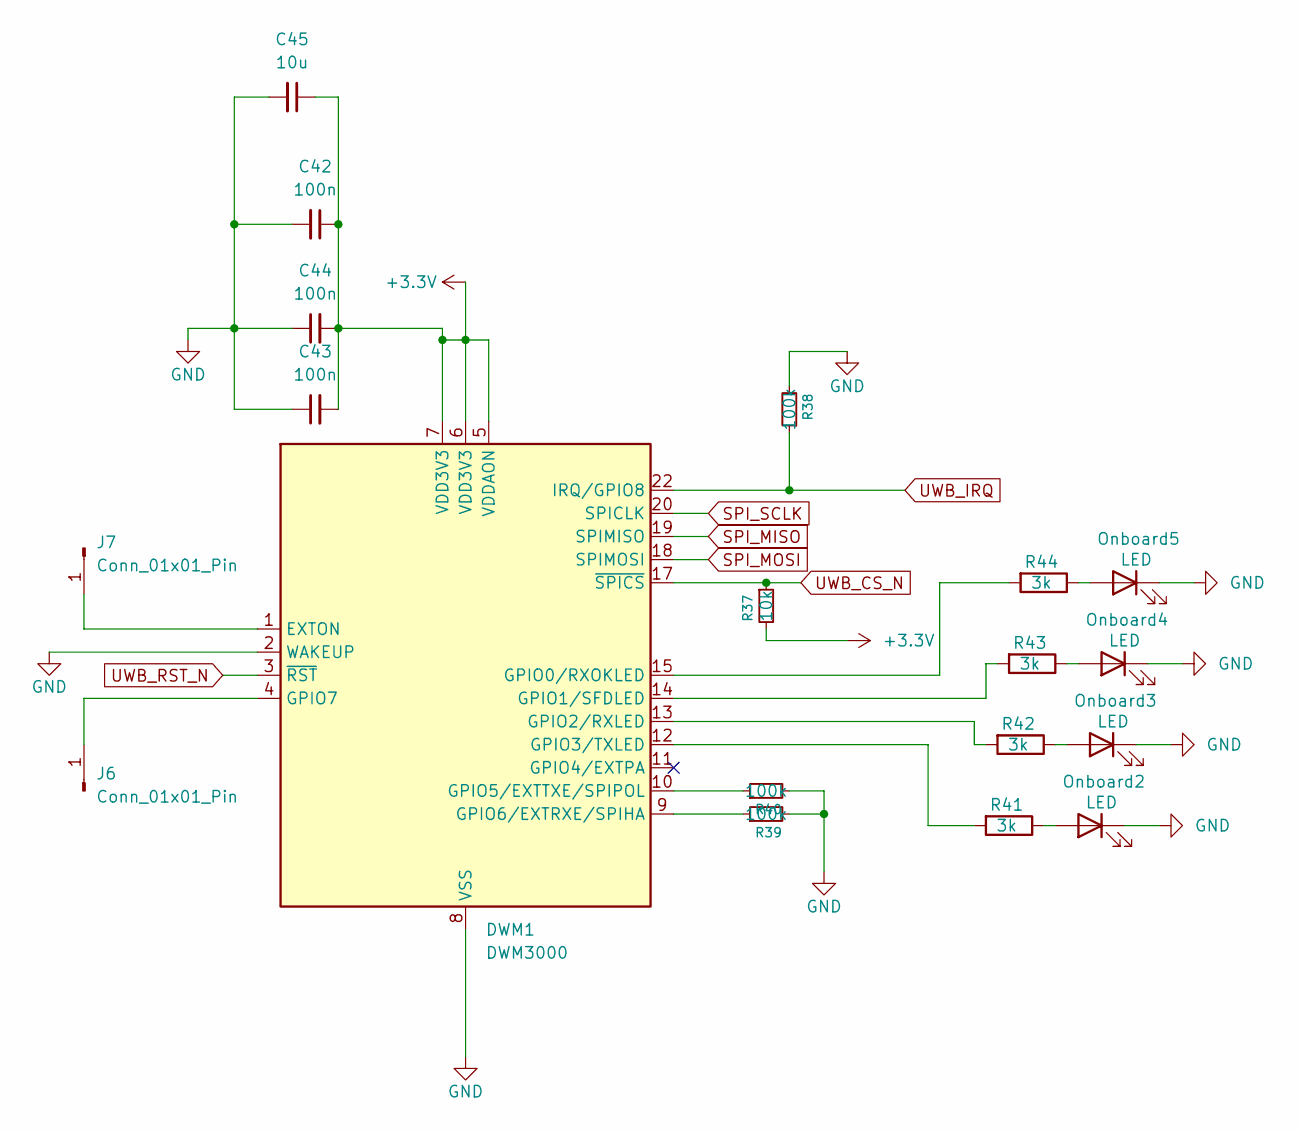
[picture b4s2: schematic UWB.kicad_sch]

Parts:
C42, C43, C44: 100n; C_0402_1005Metric_Pad0.74x0.62mm_HandSolder; LCSC Part # C14663
C45: 10u; C_0603_1608Metric_Pad1.08x0.95mm_HandSolder; LCSC Part # C14663
DWM1: DWM3000; DWM1000
J6, J7: Conn_01x01_Pin; SolderWirePad_1x01_SMD_1x2mm
Onboard2, Onboard3, Onboard4, Onboard5: LED; LED_0603_1608Metric_Pad1.05x0.95mm_HandSolder; LCSC Part # C2297
R37: 10k; R_0402_1005Metric_Pad0.72x0.64mm_HandSolder
R38, R39, R40: 100k; R_0402_1005Metric_Pad0.72x0.64mm_HandSolder
R41, R42, R43, R44: 3k; R_0402_1005Metric_Pad0.72x0.64mm_HandSolder; LCSC Part # C4211

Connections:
GND: C42.2, C43.1, C44.1, C45.2, DWM1.2 (WAKEUP), DWM1.8 (VSS), DWM1.16 (VSS), DWM1.21 (VSS), DWM1.23 (VSS), DWM1.24 (VSS), Onboard2.1 (K), Onboard3.1 (K), Onboard4.1 (K), Onboard5.1 (K), R38.2, R39.2, R40.2; also elsewhere on the board
unnamed: DWM1.1 (EXTON), J7.1 (Pin_1_1)
unnamed: DWM1.15 (GPIO0/RXOKLED), R44.2
unnamed: DWM1.14 (GPIO1/SFDLED), R43.2
unnamed: DWM1.13 (GPIO2/RXLED), R42.2
unnamed: DWM1.12 (GPIO3/TXLED), R41.2
unnamed: DWM1.10 (GPIO5/EXTTXE/SPIPOL), R40.1
unnamed: DWM1.9 (GPIO6/EXTRXE/SPIHA), R39.1
unnamed: DWM1.4 (GPIO7), J6.1 (Pin_1_1)
unnamed: Onboard2.2 (A), R41.1
unnamed: Onboard3.2 (A), R42.1
unnamed: Onboard4.2 (A), R43.1
unnamed: Onboard5.2 (A), R44.1
PS1: C42.1, C43.2, C44.2, C45.1, DWM1.5 (VDDAON), DWM1.6 (VDD3V3), DWM1.7 (VDD3V3), R37.2; also elsewhere on the board
SPI_MISO: DWM1.19 (SPIMISO); also elsewhere on the board
SPI_MOSI: DWM1.18 (SPIMOSI); also elsewhere on the board
SPI_SCLK: DWM1.20 (SPICLK); also elsewhere on the board
UWB_CS_N: DWM1.17 (~SPICS), R37.1; also elsewhere on the board
UWB_IRQ: DWM1.22 (IRQ/GPIO8), R38.1; also elsewhere on the board
UWB_RST_N: DWM1.3 (~RST); also elsewhere on the board

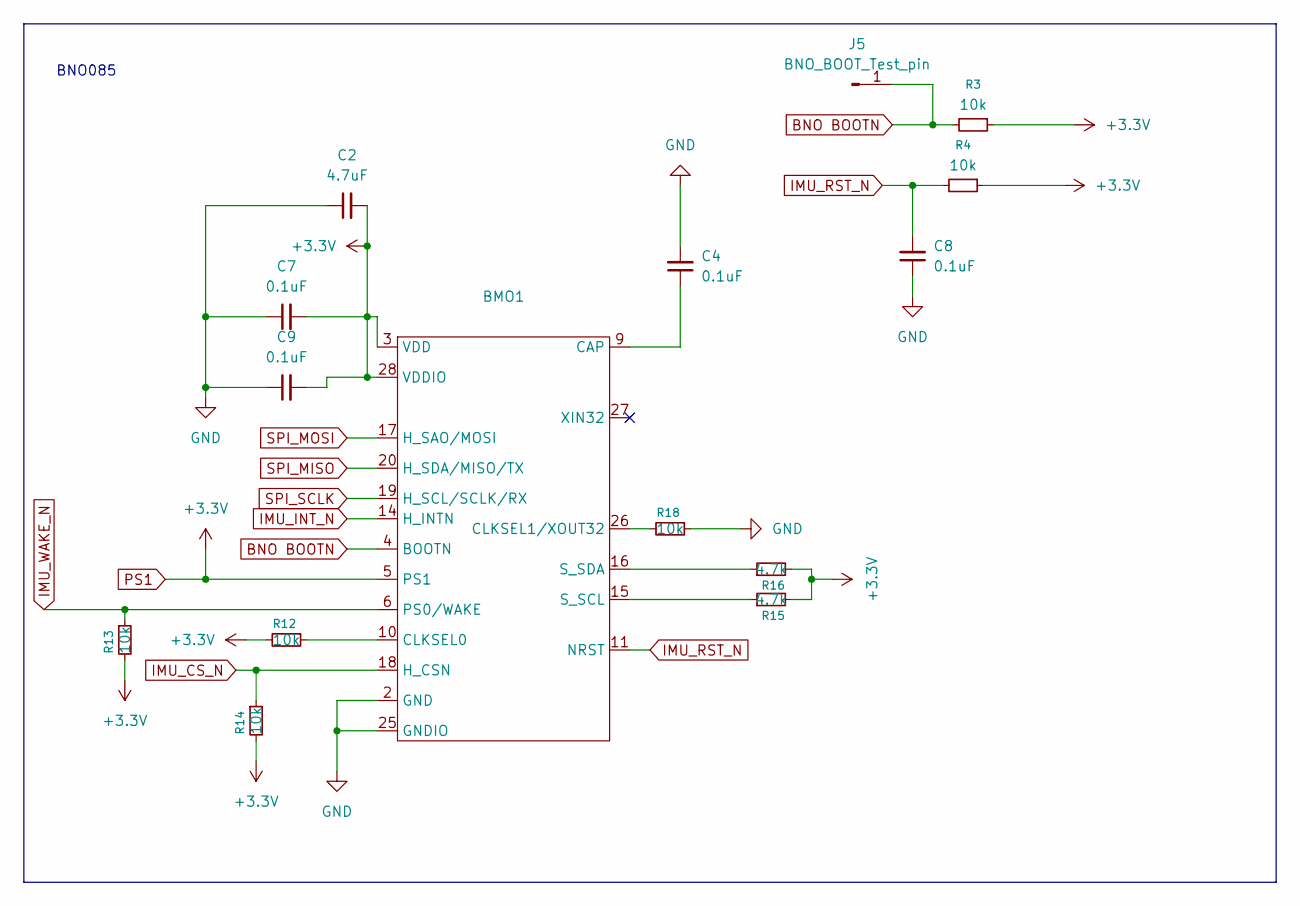
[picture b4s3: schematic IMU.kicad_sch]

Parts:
BMO1: LGA-28_5.2x3.8mm_P0.5mm
C2: 4.7uF; C_0402_1005Metric_Pad0.74x0.62mm_HandSolder
C4, C7, C8, C9: 0.1uF; C_0402_1005Metric_Pad0.74x0.62mm_HandSolder
J5: BNO_BOOT_Test_pin; SolderWirePad_1x01_SMD_1x2mm
R3, R4, R12, R13, R14, R18: 10k; R_0402_1005Metric_Pad0.72x0.64mm_HandSolder
R15, R16: 4.7k; R_0402_1005Metric_Pad0.72x0.64mm_HandSolder

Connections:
BNO BOOTN: BMO1.4 (BOOTN), J5.1 (Pin_1_1), R3.2
GND: BMO1.2 (GND), BMO1.25 (GNDIO), C2.1, C4.2, C7.1, C8.1, C9.1, R18.1; also elsewhere on the board
IMU_CS_N: BMO1.18 (H_CSN), R14.1; also elsewhere on the board
IMU_INT_N: BMO1.14 (H_INTN); also elsewhere on the board
IMU_RST_N: BMO1.11 (NRST), C8.2, R4.2; also elsewhere on the board
IMU_WAKE_N: BMO1.6 (PS0/WAKE), R13.1; also elsewhere on the board
unnamed: BMO1.9 (CAP), C4.1
unnamed: BMO1.10 (CLKSEL0), R12.1
unnamed: BMO1.26 (CLKSEL1/XOUT32), R18.2
unnamed: BMO1.15 (S_SCL), R15.1
unnamed: BMO1.16 (S_SDA), R16.1
PS1: BMO1.3 (VDD), BMO1.5 (PS1), BMO1.8 (nc), BMO1.28 (VDDIO), C2.2, C7.2, C9.2, R3.1, R4.1, R12.2, R13.2, R14.2, R15.2, R16.2; also elsewhere on the board
SPI_MISO: BMO1.20 (H_SDA/MISO/TX); also elsewhere on the board
SPI_MOSI: BMO1.17 (H_SAO/MOSI); also elsewhere on the board
SPI_SCLK: BMO1.19 (H_SCL/SCLK/RX); also elsewhere on the board

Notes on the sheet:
BNO085

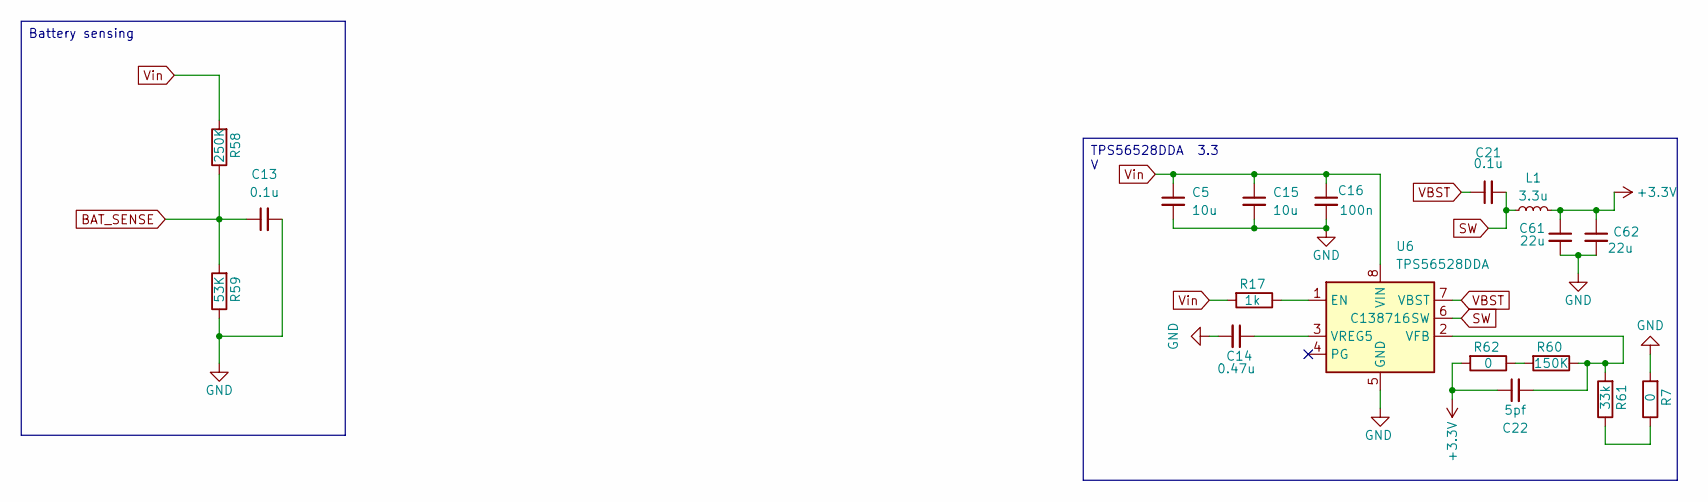
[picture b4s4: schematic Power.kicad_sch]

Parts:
C5, C15: 10u; C_0603_1608Metric_Pad1.08x0.95mm_HandSolder; LCSC Part # C15850
C13: 0.1u; C_0402_1005Metric_Pad0.74x0.62mm_HandSolder; LCSC Part # C15850
C14: 0.47u; C_0402_1005Metric_Pad0.74x0.62mm_HandSolder; LCSC Part # C1623
C16: 100n; C_0402_1005Metric_Pad0.74x0.62mm_HandSolder; LCSC Part # C15850
C21: 0.1u; C_0402_1005Metric_Pad0.74x0.62mm_HandSolder; LCSC Part # C14663
C22: 5pf; C_0402_1005Metric_Pad0.74x0.62mm_HandSolder; LCSC Part # C1653
C61, C62: 22u; C_0603_1608Metric_Pad1.08x0.95mm_HandSolder; LCSC Part # C45783
L1: 3.3u; L_Abracon_ASPI-0630LR
R7: 0; R_0603_1608Metric_Pad0.98x0.95mm_HandSolder; LCSC Part # C4216
R17: 1k; R_0402_1005Metric_Pad0.72x0.64mm_HandSolder; LCSC Part # C21190
R58: 250K; R_0402_1005Metric_Pad0.72x0.64mm_HandSolder; LCSC Part # C23182
R59: 53K; R_0402_1005Metric_Pad0.72x0.64mm_HandSolder; LCSC Part # C23182
R60: 150K; R_0603_1608Metric_Pad0.98x0.95mm_HandSolder; LCSC Part # C22807
R61: 33k; R_0603_1608Metric_Pad0.98x0.95mm_HandSolder; LCSC Part # C4216
R62: 0; R_0603_1608Metric_Pad0.98x0.95mm_HandSolder; LCSC Part # C22807
U6: TPS56528DDA; Texas_HSOP-8-1EP_3.9x4.9mm_P1.27mm_ThermalVias; LCSC Part # C138716

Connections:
BAT_SENSE: C13.1, R58.1, R59.2; also elsewhere on the board
GND: C5.2, C13.2, C14.2, C15.2, C16.2, C61.2, C62.2, R7.2, R59.1, U6.5 (GND), U6.9 (GND); also elsewhere on the board
unnamed: R60.2, R62.1
unnamed: R7.1, R61.1
unnamed: R17.1, U6.1 (EN)
unnamed: C22.2, R60.1, R61.2, U6.2 (VFB)
unnamed: C14.1, U6.3 (VREG5)
PS1: C22.1, C61.1, C62.1, L1.2, R62.2; also elsewhere on the board
SW: C21.2, L1.1, U6.6 (SW)
VBST: C21.1, U6.7 (VBST)
Vin: C5.1, C15.1, C16.1, R17.2, R58.2, U6.8 (VIN); also elsewhere on the board

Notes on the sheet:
TPS56528DDA 3.3 V
Battery sensing
